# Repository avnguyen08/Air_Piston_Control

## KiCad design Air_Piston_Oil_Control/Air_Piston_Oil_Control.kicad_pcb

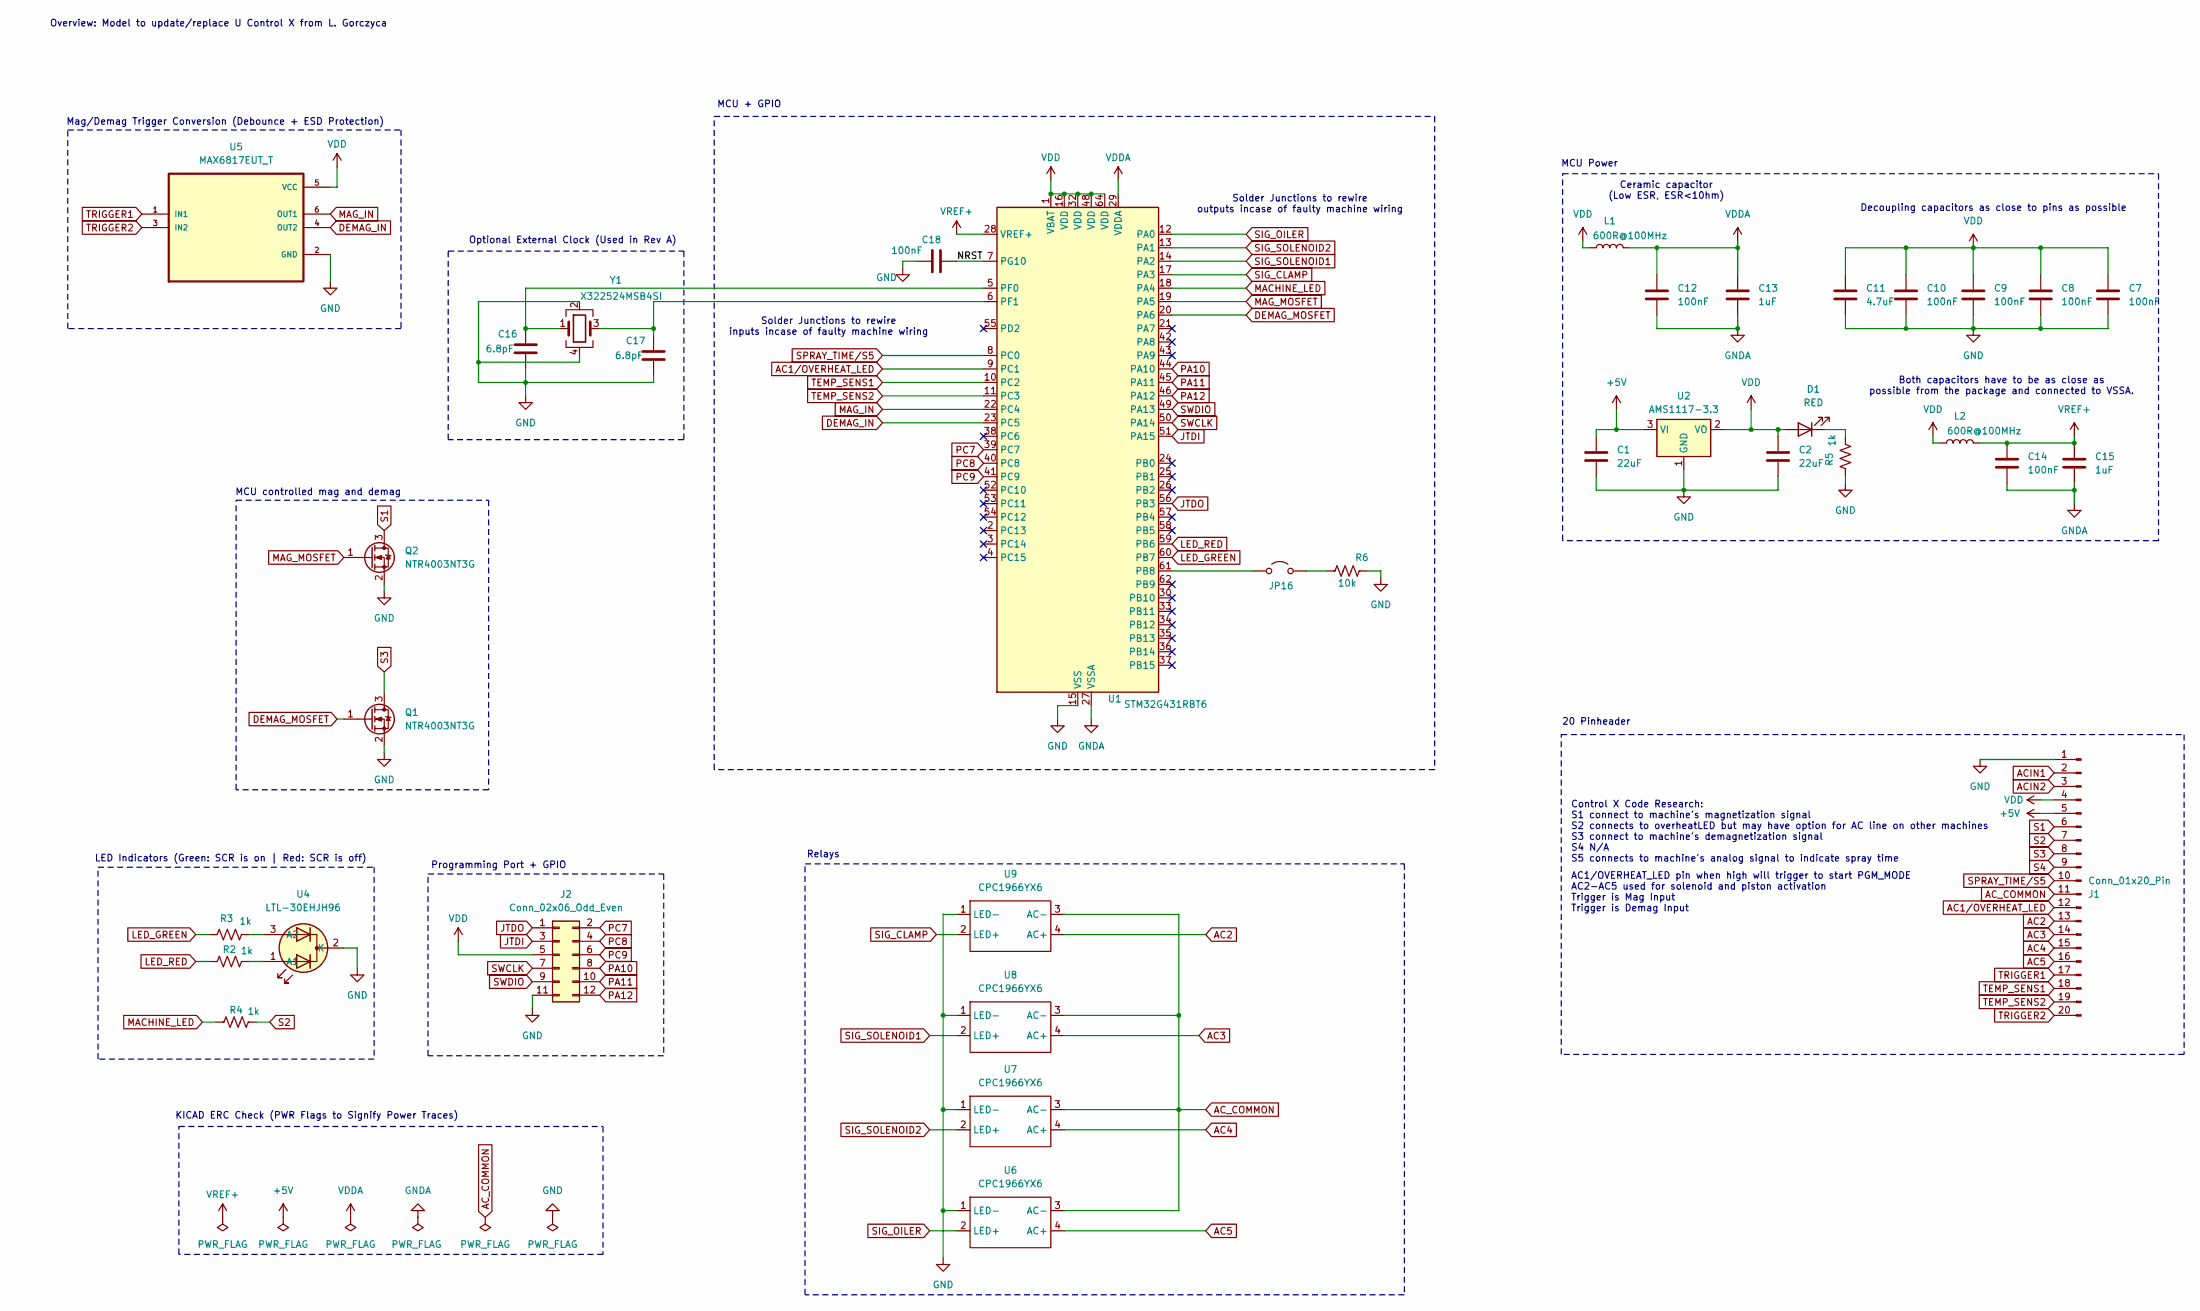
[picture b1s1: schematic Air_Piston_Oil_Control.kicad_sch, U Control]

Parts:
C1, C2: 22uF; C_0805_2012Metric
C7, C8, C9, C10, C12, C14, C18: 100nF; C_0805_2012Metric
C11: 4.7uF; C_0805_2012Metric
C13, C15: 1uF; C_0805_2012Metric
C16, C17: 6.8pF; C_0805_2012Metric
D1: RED; LED_0805_2012Metric
J1: Conn_01x20_Pin; Molex_SL_171971-0020_1x20_P2.54mm_Vertical
J2: Conn_02x06_Odd_Even; PinHeader_2x06_P2.54mm_Vertical
JP16: Jumper_2_Open; PinHeader_1x02_P2.54mm_Vertical
L1, L2: 600R@100MHz; L_0805_2012Metric
Q1, Q2: NTR4003NT3G
R2, R3, R4, R5: 1k; R_0805_2012Metric
R6: 10k; R_0805_2012Metric
U1: STM32G431RBT6; LQFP-64_10x10mm_P0.5mm
U2: AMS1117-3.3; SOT-223-3_TabPin2
U4: LTL-30EHJH96
U5: MAX6817EUT_T
U6, U7, U8, U9: CPC1966YX6
Y1: X322524MSB4SI; Crystal_SMD_3225-4Pin_3.2x2.5mm

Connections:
+5V: C1.1, J1.5, U2.3 (VI)
/NRST: C18.2, U1.7 (PG10)
AC1/OVERHEAT_LED: J1.12, U1.9 (PC1)
AC2: J1.13, U9.4 (AC+)
AC3: J1.14, U8.4 (AC+)
AC4: J1.15, U7.4 (AC+)
AC5: J1.16, U6.4 (AC+)
ACIN1: J1.2
ACIN2: J1.3
AC_COMMON: J1.11, U6.3 (AC-), U7.3 (AC-), U8.3 (AC-), U9.3 (AC-)
DEMAG_IN: U1.23 (PC5), U5.4 (OUT2)
DEMAG_MOSFET: Q1.1 (G), U1.20 (PA6)
GND: C1.2, C2.2, C7.2, C8.2, C9.2, C10.2, C11.2, C16.2, C17.2, C18.1, J1.1, J2.11, Q1.2 (S), Q2.2 (S), R5.1, R6.1, U1.15 (VSS), U1.31 (VSS), U1.47 (VSS), U1.63 (VSS), U2.1 (GND), U4.2 (K), U5.2 (GND), U6.1 (LED-), U7.1 (LED-), U8.1 (LED-), U9.1 (LED-), Y1.2, Y1.4
GNDA: C12.2, C13.2, C14.2, C15.2, U1.27 (VSSA)
JTDI: J2.3, U1.51 (PA15)
JTDO: J2.1, U1.56 (PB3)
LED_GREEN: R3.1, U1.60 (PB7)
LED_RED: R2.1, U1.59 (PB6)
MACHINE_LED: R4.1, U1.18 (PA4)
MAG_IN: U1.22 (PC4), U5.6 (OUT1)
MAG_MOSFET: Q2.1 (G), U1.19 (PA5)
unnamed: D1.1 (K), R5.2
unnamed: JP16.1 (A), U1.61 (PB8)
unnamed: JP16.2 (B), R6.2
unnamed: C16.1, U1.5 (PF0), Y1.1
unnamed: C17.1, U1.6 (PF1), Y1.3
unnamed: R2.2, U4.1 (A1)
unnamed: R3.2, U4.3 (A2)
PA10: J2.8, U1.44 (PA10)
PA11: J2.10, U1.45 (PA11)
PA12: J2.12, U1.46 (PA12)
PC7: J2.2, U1.39 (PC7)
PC8: J2.4, U1.40 (PC8)
PC9: J2.6, U1.41 (PC9)
S1: J1.6, Q2.3 (D)
S2: J1.7, R4.2
S3: J1.8, Q1.3 (D)
S4: J1.9
SIG_CLAMP: U1.17 (PA3), U9.2 (LED+)
SIG_OILER: U1.12 (PA0), U6.2 (LED+)
SIG_SOLENOID1: U1.14 (PA2), U8.2 (LED+)
SIG_SOLENOID2: U1.13 (PA1), U7.2 (LED+)
SPRAY_TIME/S5: J1.10, U1.8 (PC0)
SWCLK: J2.7, U1.50 (PA14)
SWDIO: J2.9, U1.49 (PA13)
TEMP_SENS1: J1.18, U1.10 (PC2)
TEMP_SENS2: J1.19, U1.11 (PC3)
TRIGGER1: J1.17, U5.1 (IN1)
TRIGGER2: J1.20, U5.3 (IN2)
VDD: C2.1, C7.1, C8.1, C9.1, C10.1, C11.1, D1.2 (A), J1.4, J2.5, L1.2, L2.1, U1.1 (VBAT), U1.16 (VDD), U1.32 (VDD), U1.48 (VDD), U1.64 (VDD), U2.2 (VO), U5.5 (VCC)
VDDA: C12.1, C13.1, L1.1, U1.29 (VDDA)
VREF+: C14.1, C15.1, L2.2, U1.28 (VREF+)

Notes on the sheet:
MCU controlled mag and demag
Control X Code Research: S1 connect to machine's magnetization signal S2 connects to overheatLED but may have option for AC line on other machines S3 connect to machine's demagnetization signal S4 N/A S5 connects to machine's analog signal to indicate spray time
20 Pinheader
MCU + GPIO
KICAD ERC Check (PWR Flags to Signify Power Traces)
Relays
Solder Junctions to rewire inputs incase of faulty machine wiring
Decoupling capacitors as close to pins as possible
Optional External Clock (Used in Rev A)
AC1/OVERHEAT_LED pin when high will trigger to start PGM_MODE AC2-AC5 used for solenoid and piston activation Trigger is Mag Input Trigger is Demag Input
Solder Junctions to rewire outputs incase of faulty machine wiring
MCU Power
Mag/Demag Trigger Conversion (Debounce + ESD Protection)
Both capacitors have to be as close as possible from the package and connected to VSSA.
Ceramic capacitor (Low ESR, ESR<10hm)
Programming Port + GPIO
LED Indicators (Green: SCR is on | Red: SCR is off)
Overview: Model to update/replace U Control X from L. Gorczyca

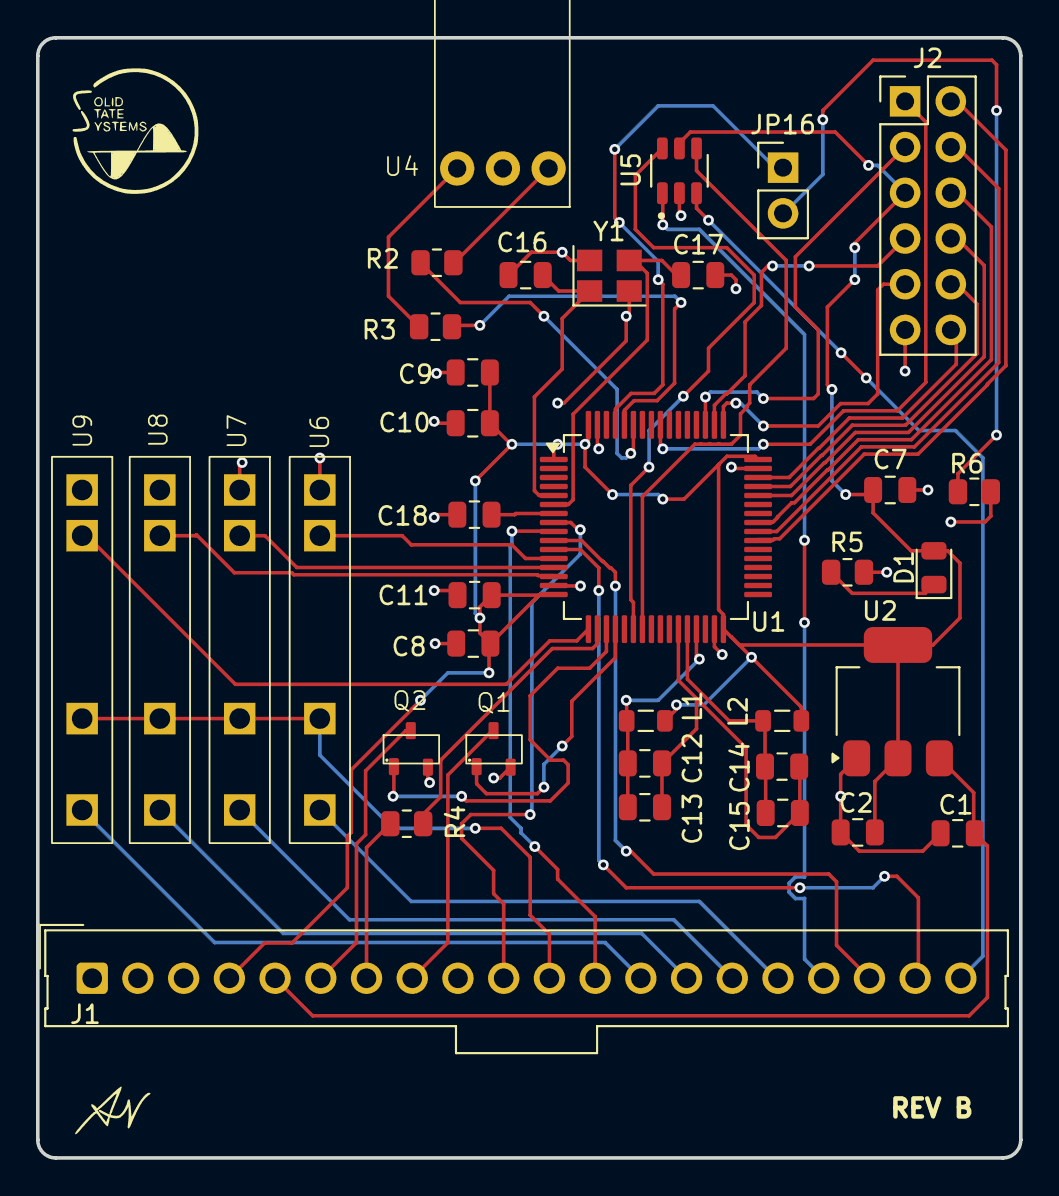
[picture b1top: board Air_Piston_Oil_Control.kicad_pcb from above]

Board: 2 copper layers, 54.6 x 62.2 mm, 36 parts (0 on the bottom side), 49 nets.

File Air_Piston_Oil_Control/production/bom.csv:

Designator,Footprint,Quantity,Value,LCSC Part #
"C1, C2",0805,2,22uF,
"C10, C12, C14, C18, C7, C8, C9",0805,7,100nF,
C11,0805,1,4.7uF,
"C13, C15",0805,2,1uF,
"C16, C17",0805,2,6.8pF,
D1,0805,1,RED,
J1,Molex_SL_171971-0020_1x20_P2.54mm_Vertical,1,Conn_01x20_Pin,
J2,PinHeader_2x06_P2.54mm_Vertical,1,Conn_02x06_Odd_Even,
JP16,PinHeader_1x02_P2.54mm_Vertical,1,Jumper_2_Open,
"L1, L2",0805,2,600R@100MHz,
"Q1, Q2",NTR4003NT3G,2,NTR4003NT3G,
"R2, R3, R4, R5",0805,4,1k,
R6,0805,1,10k,
U1,LQFP-64_10x10mm_P0.5mm,1,STM32G431RBT6,
U2,SOT-223-3_TabPin2,1,AMS1117-3.3,
U4,LTL-30EHJH96,1,LTL-30EHJH96,
U5,MAX6817EUT_T,1,MAX6817EUT_T,
"U6, U7, U8, U9",CPC1966YX6,4,CPC1966YX6,
Y1,Crystal_SMD_3225-4Pin_3.2x2.5mm,1,X322524MSB4SI,

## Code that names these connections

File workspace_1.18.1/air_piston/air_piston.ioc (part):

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Mcu.Name=STM32G431R(6-8-B)Tx
Mcu.Package=LQFP64
Mcu.UserName=STM32G431RBTx
PA0.GPIOParameters=GPIO_Label
PA0.GPIO_Label=Sig_Oiler
PA0.Signal=GPIO_Output
PA1.GPIOParameters=GPIO_Label
PA1.GPIO_Label=Sig_Solenoid2
PA1.Signal=GPIO_Output
PA2.GPIOParameters=GPIO_Label
PA2.GPIO_Label=Sig_Solenoid1
PA2.Signal=GPIO_Output
PA3.GPIOParameters=GPIO_Label
PA3.GPIO_Label=Sig_Clamp
PA3.Signal=GPIO_Output
PA4.GPIOParameters=GPIO_Label
PA4.GPIO_Label=Machine_LED
PA4.Signal=GPIO_Output
PA5.GPIOParameters=GPIO_Label
PA5.GPIO_Label=Mag_Mosfet
PA5.Signal=GPIO_Output
PA6.GPIOParameters=GPIO_Label
PA6.GPIO_Label=Demag_Mosfet
PA6.Signal=GPIO_Output
PB6.GPIOParameters=GPIO_Label
PB6.GPIO_Label=GREEN_LED
PB6.Signal=GPIO_Output
PB7.GPIOParameters=GPIO_Label
PB7.GPIO_Label=RED_LED
PB7.Signal=GPIO_Output
PC0.GPIOParameters=GPIO_Label
PC0.GPIO_Label=Spray_Time
PC0.Mode=IN6-Single-Ended
PC0.Signal=ADC1_IN6
PC1.GPIOParameters=GPIO_PuPd,GPIO_Label
PC1.GPIO_Label=AC1/Over_Heat_LED
PC1.GPIO_PuPd=GPIO_PULLDOWN
PC1.Signal=GPIO_Input
PC2.GPIOParameters=GPIO_Label
PC2.GPIO_Label=Temp_Sensor1
PC2.Mode=IN8-Single-Ended
PC2.Signal=ADC1_IN8
PC3.GPIOParameters=GPIO_Label
PC3.GPIO_Label=Temp_Sensor2
PC3.Mode=IN9-Single-Ended
PC3.Signal=ADC1_IN9
PC4.GPIOParameters=GPIO_Label
PC4.GPIO_Label=Mag_In
PC4.Signal=GPIO_Input
PC5.GPIOParameters=GPIO_Label
PC5.GPIO_Label=Demag_In
PC5.Signal=GPIO_Input
PF0-OSC_IN.Mode=HSE-External-Oscillator
PF0-OSC_IN.Signal=RCC_OSC_IN
PF1-OSC_OUT.Mode=HSE-External-Oscillator
PF1-OSC_OUT.Signal=RCC_OSC_OUT
RCC.HSE_VALUE=24000000
RCC.SYSCLKFreq_VALUE=16000000
board=custom

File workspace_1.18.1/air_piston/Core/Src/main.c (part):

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int Temp_Sensor1;
int Temp_Sensor2;

int Trigger1=10;
int Trigger2=19;

int SCR_STATUS;

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
	    Temp_Check();
	    if(SCR_STATUS!=0){
	      if((HAL_GPIO_ReadPin(Mag_In_GPIO_Port, Mag_In_Pin) == GPIO_PIN_RESET)&&(Time_Delay1>0)){
	        AutoMag(); // Magnatize
	      }
	      if((HAL_GPIO_ReadPin(Demag_In_GPIO_Port, Demag_In_Pin) == GPIO_PIN_RESET)&&(Time_Delay1>0)){
	        Demag(); // De-Magnatize
	      }
	      if((HAL_GPIO_ReadPin(Mag_In_GPIO_Port, Mag_In_Pin) == GPIO_PIN_RESET)&&(Time_Delay1==0)){
	        Std_Mag(); // Magnatize
	      }

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  __HAL_RCC_GPIOB_CLK_ENABLE();

  /*Configure GPIO pin Output Level */
  HAL_GPIO_WritePin(GPIOA, Sig_Oiler_Pin|Sig_Solenoid2_Pin|Sig_Solenoid1_Pin|Sig_Clamp_Pin
                          |Machine_LED_Pin|Mag_Mosfet_Pin|Demag_Mosfet_Pin, GPIO_PIN_RESET);

  /*Configure GPIO pin Output Level */
  HAL_GPIO_WritePin(GPIOB, GREEN_LED_Pin|RED_LED_Pin, GPIO_PIN_RESET);
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  GPIO_InitStruct.Pull = GPIO_PULLDOWN;
  HAL_GPIO_Init(AC1_Over_Heat_LED_GPIO_Port, &GPIO_InitStruct);

  /*Configure GPIO pins : Sig_Oiler_Pin Sig_Solenoid2_Pin Sig_Solenoid1_Pin Sig_Clamp_Pin
                           Machine_LED_Pin Mag_Mosfet_Pin Demag_Mosfet_Pin */
  GPIO_InitStruct.Pin = Sig_Oiler_Pin|Sig_Solenoid2_Pin|Sig_Solenoid1_Pin|Sig_Clamp_Pin
                          |Machine_LED_Pin|Mag_Mosfet_Pin|Demag_Mosfet_Pin;
  GPIO_InitStruct.Mode = GPIO_MODE_OUTPUT_PP;
  GPIO_InitStruct.Pull = GPIO_NOPULL;
  GPIO_InitStruct.Speed = GPIO_SPEED_FREQ_LOW;
  HAL_GPIO_Init(GPIOA, &GPIO_InitStruct);

  /*Configure GPIO pins : Mag_In_Pin Demag_In_Pin */
  GPIO_InitStruct.Pin = Mag_In_Pin|Demag_In_Pin;
  GPIO_InitStruct.Mode = GPIO_MODE_INPUT;
  GPIO_InitStruct.Pull = GPIO_NOPULL;
  HAL_GPIO_Init(GPIOC, &GPIO_InitStruct);
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
}

#define Mag_Mosfet_Pin GPIO_PIN_5
#define Mag_Mosfet_GPIO_Port GPIOA
void Mag_Shot()
{
	HAL_GPIO_WritePin(Mag_Mosfet_GPIO_Port, Mag_Mosfet_Pin, GPIO_PIN_SET); // Mag Shot
	HAL_Delay(100); // Delay Time
	HAL_GPIO_WritePin(Mag_Mosfet_GPIO_Port, Mag_Mosfet_Pin, GPIO_PIN_RESET); // Mag Shot
}

void Demag()
{
   Clamp();
  HAL_Delay(1000);
  HAL_GPIO_WritePin(Demag_Mosfet_GPIO_Port, Demag_Mosfet_Pin, GPIO_PIN_SET); // DE-Mag Shot
  HAL_Delay(100); // Delay Time
  HAL_GPIO_WritePin(Mag_Mosfet_GPIO_Port, Mag_Mosfet_Pin, GPIO_PIN_RESET); // De-Mag Shot
  HAL_Delay(25000);
  UnClamp();
}

void Water_On()
{
	HAL_GPIO_WritePin(Sig_Solenoid1_GPIO_Port, Sig_Solenoid1_Pin, GPIO_PIN_RESET); // Water Solenoid 1
	HAL_GPIO_WritePin(Sig_Solenoid2_GPIO_Port, Sig_Solenoid2_Pin, GPIO_PIN_SET); // Water Solenoid 2
}

void Water_Off()
{
	HAL_GPIO_WritePin(Sig_Solenoid1_GPIO_Port, Sig_Solenoid1_Pin, GPIO_PIN_SET); // Water Solenoid 1
  HAL_GPIO_WritePin(Sig_Solenoid2_GPIO_Port, Sig_Solenoid2_Pin, GPIO_PIN_RESET); // Water Solenoid 2
}

void Clamp()
{
	HAL_GPIO_WritePin(Sig_Clamp_GPIO_Port, Sig_Clamp_Pin, GPIO_PIN_SET); // Clamp Head

}

void UnClamp()
{
	HAL_GPIO_WritePin(Sig_Clamp_GPIO_Port, Sig_Clamp_Pin, GPIO_PIN_RESET); // Clamp Head
}

void Piss()
{

	HAL_GPIO_WritePin(Sig_Oiler_GPIO_Port, Sig_Oiler_Pin, GPIO_PIN_SET); // Oiler On
	HAL_Delay(D_Time); // Delay Time
	HAL_GPIO_WritePin(Sig_Oiler_GPIO_Port, Sig_Oiler_Pin, GPIO_PIN_RESET);
}

void Temp_Check()
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}

void SCR_ON(){
	HAL_GPIO_WritePin(Machine_LED_GPIO_Port, Machine_LED_Pin, GPIO_PIN_RESET);
	SCR_STATUS=1;
}

void SCR_OFF(){
	HAL_GPIO_WritePin(Machine_LED_GPIO_Port, Machine_LED_Pin, GPIO_PIN_SET);
	SCR_STATUS=0;
}

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
  Temp_Check();
  if(SCR_STATUS!=0){
    if((HAL_GPIO_ReadPin(Demag_In_GPIO_Port, Demag_In_Pin) == GPIO_PIN_RESET)&&(Time_Delay1>0)){
      Piss(); // Magnetize
      HAL_Delay(D_Time); // Return Delay Time
    }
    if(HAL_GPIO_ReadPin(Mag_In_GPIO_Port, Mag_In_Pin) == GPIO_PIN_RESET){
      Clamp();
      MAG_SETUP(); // De-Magnatize
      UnClamp();
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void MAG_SETUP()
{
   while(HAL_GPIO_ReadPin(AC1_Over_Heat_LED_GPIO_Port, AC1_Over_Heat_LED_Pin) == GPIO_PIN_SET){
     if(HAL_GPIO_ReadPin(Demag_In_GPIO_Port, Demag_In_Pin) == GPIO_PIN_RESET){
       break;
     }
     if(HAL_GPIO_ReadPin(Mag_In_GPIO_Port, Mag_In_Pin) == GPIO_PIN_RESET){
       Temp_Check();
       if(SCR_STATUS!=0){
         Mag_Shot();
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
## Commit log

2025-07-15 working
2025-07-17 manufacture ready
2025-07-28 Ver B manufacturing, removed solder pads
2025-08-18 adding stm32 firmware workspace
2025-08-30 syncing files

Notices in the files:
workspace_1.18.1/air_piston/Core/Src/main.c:
Copyright (c) 2025 STMicroelectronics.
All rights reserved.
This software is licensed under terms that can be found in the LICENSE file
